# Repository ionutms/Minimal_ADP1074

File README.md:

# Minimal_ADP1074

## Overview

This repository contains a minimal KiCad design project for the Analog Devices ADP1074, a current mode synchronous flyback controller with iCoupler-isolated feedback. The project includes schematic designs and PCB layout files for implementing this isolated power supply controller.

## Disclaimer

> [!NOTE]
> This project is provided "as is" and without any warranty, express or implied. For more details, please see the [LICENSE](LICENSE) file.

## About the ADP1074

The ADP1074 from Analog Devices is a current mode synchronous flyback controller with integrated iCoupler technology for isolated feedback. It is designed for high-efficiency, compact isolated DC-to-DC converters.

Key features include:

- **Integrated iCoupler Technology:** Provides isolated feedback without the need for an optocoupler, improving reliability and performance.
- **Current Mode Control:** Offers excellent line and load transient response.
- **Synchronous Rectification:** Improves efficiency by replacing the secondary-side diode with a MOSFET.
- **Programmable Frequency:** The switching frequency can be adjusted to optimize for size or efficiency.
- **Protection Features:** Includes overcurrent protection (OCP), overvoltage protection (OVP), and thermal shutdown.
- **Wide Input Voltage Range:** Supports a broad range of input voltages, making it suitable for various applications.
- **Package:** Available in a 24-lead LFCSP package.

## Project Structure

```
minimal_adp1074/
├── minimal_adp1074.kicad_pro       # Project configuration file
├── minimal_adp1074.kicad_sch       # Main schematic file
├── minimal_adp1074.kicad_pcb       # PCB layout file
├── fp-lib-table                    # Footprint library table
├── sym-lib-table                   # Symbol library table
├── docs/                           # Documentation files
│   ├── bom/                        # Bill of Materials
│   │   └── minimal_adp1074_ibom.html # Interactive BOM file
│   ├── pictures/                   # Images and photos
│   │   ├── 1_minimal_adp1074_side.png
│   │   ├── 2_minimal_adp1074_top.png
│   │   ├── 3_minimal_adp1074_bottom.png
│   │   ├── 4_minimal_adp1074_left.png
│   │   └── 5_minimal_adp1074_right.png
│   └── schematics/                 # Schematic PDF exports
│       └── minimal_adp1074_schematics.pdf
└── KiCAD_Symbols_Generator/        # Submodule for symbol generation from CSV data
```

## Project Features

This design provides a minimal implementation of the ADP1074 with:

- Proper power supply connections
- Isolated feedback using integrated iCoupler technology
- Synchronous rectification for high efficiency
- Standard footprint for the 24-pin LFCSP package

## Getting Started

### Prerequisites

- [KiCad EDA](https://www.kicad.org/) version 9.0 or later installed on your system
- Git (for cloning the repository and submodule management)

### Opening the Project

1. **Clone the repository** (including submodules):
   ```bash
   git clone --recursive https://github.com/ionutms/Minimal_ADP1074.git
   ```
   
   If you've already cloned the repository without submodules, initialize them with:
   ```bash
   git submodule init
   git submodule update
   ```

2. **Open the project in KiCad**:
   - Launch KiCad
   - Click "Open Existing Project"
   - Navigate to the cloned repository folder
   - Select the `minimal_adp1074.kicad_pro` file

3. **Explore the design**:
   - Open the schematic editor to view the circuit design
   - Open the PCB editor to view the board layout
   - Review the symbol and footprint libraries used in the design

### Project Files

- **Main schematic**: `minimal_adp1074.kicad_sch` - Contains the primary circuit design with the ADP1074 and support components
- **PCB layout**: `minimal_adp1074.kicad_pcb` - Physical board design file with proper component placement
- **Project configuration**: `minimal_adp1074.kicad_pro` - KiCad project settings

## Dependencies

This project has the following dependencies:

### 1. KiCAD Symbols Generator

This repository uses [KiCAD_Symbols_Generator](https://github.com/ionutms/KiCAD_Symbols_Generator) as a submodule for custom symbol generation.

To initialize the submodule after cloning this repository:

```bash
git submodule update --init --recursive
```

### 2. 3D Models

This project requires the [3D_Models_Vault](https://github.com/ionutms/3D_Models_Vault) repository for 3D models.

#### Setup for KiCAD 9:

1. Clone the 3D models repository:
   ```bash
   git clone https://github.com/ionutms/3D_Models_Vault.git
   ```

2. In KiCAD 9, add an environment variable:
   - Variable name: `KICAD9_3D_MODELS_VAULT`
   - Variable value: Full path to where you cloned the 3D_Models_Vault repository

## Usage

After setting up the dependencies, open the project in KiCad 9 to access all features including the 3D models.

## Symbol Generator Submodule

This project includes the KiCAD_Symbols_Generator as a submodule, which provides tools for generating KiCad symbols from CSV data files. For more information on using this tool, see the [KiCAD_Symbols_Generator documentation](minimal_adp1074/KiCAD_Symbols_Generator/README.md).

## Documentation

The `docs` folder contains:
- Schematic PDF exports
- Images and photos of the design

## Visuals

The following images showcase the PCB design from different perspectives:

*Top View of the PCB*

*Side View of the PCB*

*Bottom View of the PCB*

*Left View of the PCB*

*Right View of the PCB*

## License

This project is licensed under the MIT License - see the [LICENSE](LICENSE) file for details.

## References

- [ADP1074 Datasheet](https://www.analog.com/media/en/technical-documentation/data-sheets/ADP1074.pdf)
- [KiCad EDA](https://www.kicad.org/)

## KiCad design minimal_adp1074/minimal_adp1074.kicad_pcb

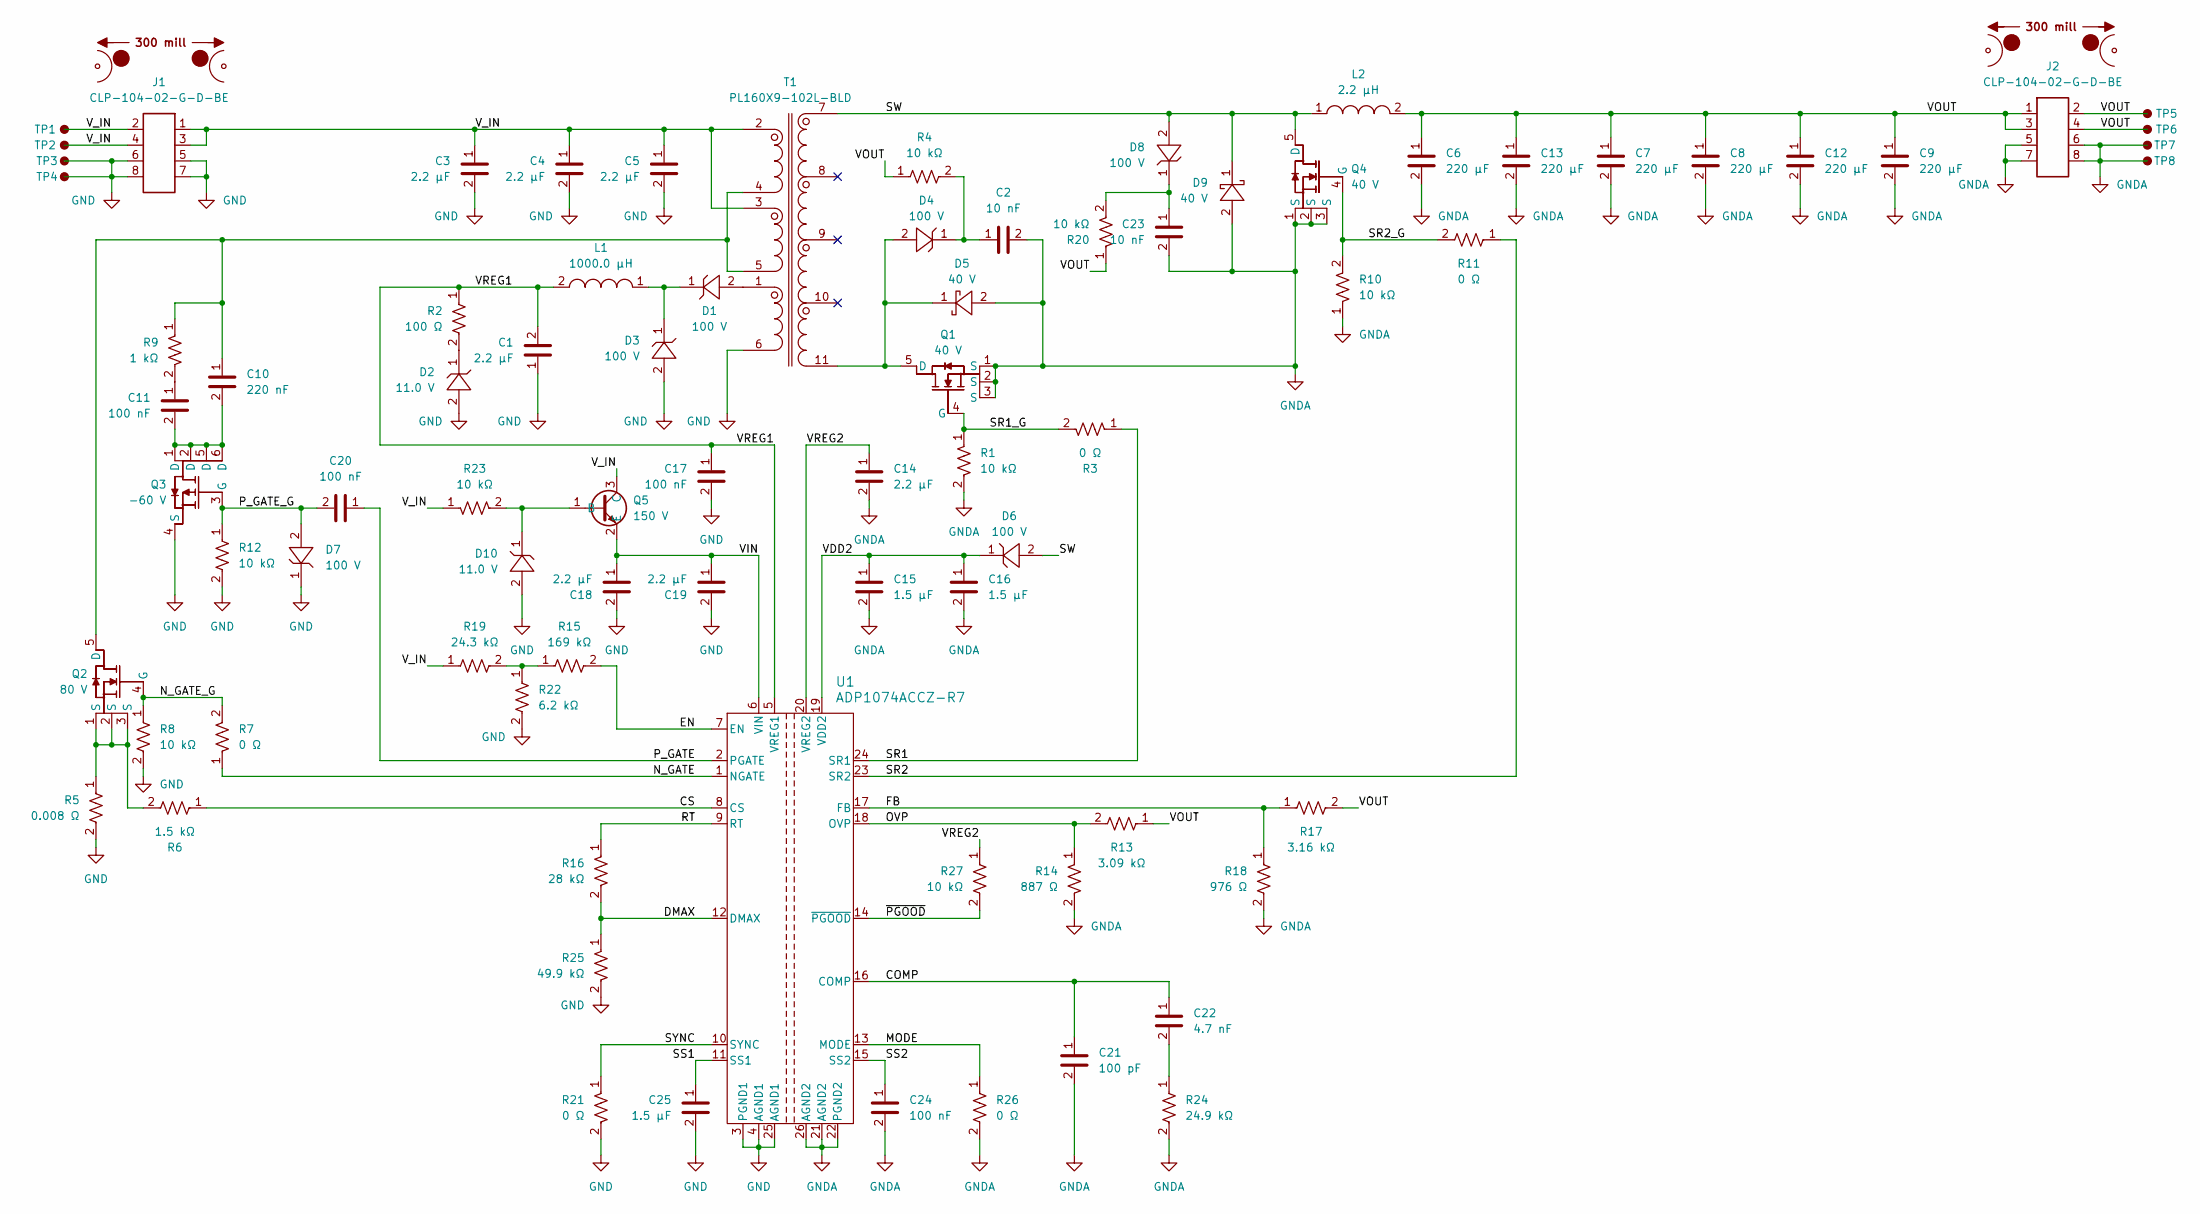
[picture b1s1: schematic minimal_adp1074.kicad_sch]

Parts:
C1, C14, C18, C19: 2.2 µF; C_0603_1608Metric; Tolerance 20%; Voltage Rating 35V; MPN C1005X5R1V225M050BC
C2, C23: 10 nF; C_0402_1005Metric; Tolerance 10%; Voltage Rating 50V; MPN GCM155R71H103KA55D
C3, C4, C5: 2.2 µF; C_1206_3216Metric; Tolerance 10%; Voltage Rating 50V; MPN KGM31HR71H225KU
C6, C7, C8, C9, C12, C13: 220 µF; C_1206_3216Metric; Tolerance 20%; Voltage Rating 6.3V; MPN GRM31CR60J227ME11K
C10: 220 nF; C_0603_1608Metric; Tolerance 10%; Voltage Rating 50V; MPN GCM188R71H224KA64D
C11, C17, C20, C24: 100 nF; C_0402_1005Metric; Tolerance 10%; Voltage Rating 50V; MPN GCM155R71H104KE02D
C15, C16, C25: 1.5 µF; C_0603_1608Metric; Tolerance 20%; Voltage Rating 35V; MPN C1005X5R1V155M050BC
C21: 100 pF; C_0402_1005Metric; Tolerance 1%; Voltage Rating 50V; MPN GCM1555C1H101FA16D
C22: 4.7 nF; C_0402_1005Metric; Tolerance 10%; Voltage Rating 50V; MPN GCM155R71H472KA37D
D1, D3, D4, D6, D7, D8: 100 V; SOD323; MPN 1N4148WX-TP
D2, D10: 11.0 V; SOD_123; MPN BZT52C11-7-F
D5, D9: 40 V; SMA; MPN B240A-13-F
J1, J2: CLP-104-02-G-D-BE; Current Rating (A) 5.2; Voltage Rating (V) 300; MPN CLP-104-02-G-D-BE
L1: 1000.0 µH; CB2518T; Tolerance ±10%; MPN CB2518T102K
L2: 2.2 µH; 74439369; Tolerance ±20%; MPN 74439369022
MB1, MB2: mouse-bite-50mil-300mil
Q1, Q4: 40 V; TDSON-8 FL; MPN BSC014N04LSI
Q2: 80 V; PowerPAK SO-8 Single; MPN SIR680DP-T1-RE3
Q3: -60 V; SOT-26; MPN ZXMP6A17E6TA
Q5: 150 V; SOT23-3; MPN FMMT625TA
R1, R4, R8, R10, R12, R20, R23, R27: 10 kΩ; R_0402_1005Metric; Tolerance 1%; Voltage Rating 50V; MPN ERJ-2RKF1002X
R2: 100 Ω; R_0402_1005Metric; Tolerance 1%; Voltage Rating 50V; MPN ERJ-2RKF1000X
R3, R7, R11, R21, R26: 0 Ω; R_0402_1005Metric; Tolerance 5%; Voltage Rating 50V; MPN ERJ-2GE0R00X
R5: 0.008 Ω; R_1206_3216Metric; Tolerance 1%; Voltage Rating 200V; MPN PMR18EZPFU8L00
R6: 1.5 kΩ; R_0402_1005Metric; Tolerance 1%; Voltage Rating 50V; MPN ERJ-2RKF1501X
R9: 1 kΩ; R_0402_1005Metric; Tolerance 1%; Voltage Rating 50V; MPN ERJ-2RKF1001X
R13: 3.09 kΩ; R_0402_1005Metric; Tolerance 1%; Voltage Rating 50V; MPN ERJ-2RKF3091X
R14: 887 Ω; R_0402_1005Metric; Tolerance 1%; Voltage Rating 50V; MPN ERJ-2RKF8870X
R15: 169 kΩ; R_0402_1005Metric; Tolerance 1%; Voltage Rating 50V; MPN ERJ-2RKF1693X
R16: 28 kΩ; R_0402_1005Metric; Tolerance 1%; Voltage Rating 50V; MPN ERJ-2RKF2802X
R17: 3.16 kΩ; R_0402_1005Metric; Tolerance 1%; Voltage Rating 50V; MPN ERJ-2RKF3161X
R18: 976 Ω; R_0402_1005Metric; Tolerance 1%; Voltage Rating 50V; MPN ERJ-2RKF9760X
R19: 24.3 kΩ; R_0402_1005Metric; Tolerance 1%; Voltage Rating 50V; MPN ERJ-2RKF2432X
R22: 6.2 kΩ; R_0402_1005Metric; Tolerance 1%; Voltage Rating 50V; MPN ERJ-2RKF6201X
R24: 24.9 kΩ; R_0402_1005Metric; Tolerance 1%; Voltage Rating 50V; MPN ERJ-2RKF2492X
R25: 49.9 kΩ; R_0402_1005Metric; Tolerance 1%; Voltage Rating 50V; MPN ERJ-2RKF4992X
T1: PL160X9-102L-BLD; PL160X9-102L; Tolerance ±10%; MPN PL160X9-102L-BLD
TP1, TP2, TP3, TP4, TP5, TP6, TP7, TP8: TestPoint; TestPoint_THTPad_Castelated
U1: ADP1074ACCZ-R7; CC-24-6_ADI; MPN ADP1074ACCZ-R7

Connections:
/COMP: C21.1, C22.1, U1.16 (COMP)
/CS: R6.1, U1.8 (CS)
/DMAX: R16.2, R25.1, U1.12 (DMAX)
/EN: R15.2, U1.7 (EN)
/FB: R17.1, R18.1, U1.17 (FB)
/MODE: R26.1, U1.13 (MODE)
/N_GATE: R7.1, U1.1 (NGATE)
/N_GATE_G: Q2.4 (G), R7.2, R8.1
/OVP: R13.2, R14.1, U1.18 (OVP)
/P_GATE: C20.1, U1.2 (PGATE)
/P_GATE_G: C20.2, D7.2, Q3.3 (G), R12.1
/RT: R16.1, U1.9 (RT)
/SR1: R3.1, U1.24 (SR1)
/SR1_G: Q1.4 (G), R1.1, R3.2
/SR2: R11.1, U1.23 (SR2)
/SR2_G: Q4.4 (G), R10.2, R11.2
/SS1: C25.1, U1.11 (SS1)
/SS2: C24.1, U1.15 (SS2)
/SW: D6.2, D8.2, D9.1, L2.1, Q4.5 (D), T1.7
/SYNC: R21.1, U1.10 (SYNC)
/VDD2: C15.1, C16.1, D6.1, U1.19 (VDD2)
/VIN: C18.1, C19.1, Q5.2 (E), U1.6 (VIN)
/VOUT: C6.1, C7.1, C8.1, C9.1, C12.1, C13.1, J2.1, J2.2, J2.3, J2.4, L2.2, R4.1, R13.1, R17.2, R20.1, TP5.1, TP6.1
/VREG1: C1.2, C17.1, L1.2, R2.1, U1.5 (VREG1)
/VREG2: C14.1, R27.1, U1.20 (VREG2)
/V_IN: C3.1, C4.1, C5.1, J1.1, J1.2, J1.3, J1.4, Q5.3 (C), R19.1, R23.1, T1.2, T1.3, TP1.1, TP2.1
/~PGOOD: R27.2, U1.14 (~PGOOD)
GND: C1.1, C3.2, C4.2, C5.2, C17.2, C18.2, C19.2, C25.2, D2.2, D3.2, D7.1, D10.2, J1.5, J1.6, J1.7, J1.8, Q3.4 (S), R5.2, R8.2, R12.2, R21.2, R22.2, R25.2, T1.6, TP3.1, TP4.1, U1.3 (PGND1), U1.4 (AGND1), U1.25 (AGND1)
GNDA: C2.2, C6.2, C7.2, C8.2, C9.2, C12.2, C13.2, C14.2, C15.2, C16.2, C21.2, C23.2, C24.2, D5.2, D9.2, J2.5, J2.6, J2.7, J2.8, Q1.1 (S), Q1.2 (S), Q1.3 (S), Q4.1 (S), Q4.2 (S), Q4.3 (S), R1.2, R10.1, R14.2, R18.2, R24.2, R26.2, TP7.1, TP8.1, U1.21 (AGND2), U1.22 (PGND2), U1.26 (AGND2)
unnamed: C2.1, D4.1, R4.2
unnamed: C10.2, C11.2, Q3.1 (D), Q3.2 (D), Q3.5 (D), Q3.6 (D)
unnamed: C11.1, R9.2
unnamed: C22.2, R24.1
unnamed: C23.1, D8.1, R20.2
unnamed: D1.1, D3.1, L1.1
unnamed: D1.2, T1.1
unnamed: D2.1, R2.2
unnamed: D4.2, D5.1, Q1.5 (D), T1.11
unnamed: C10.1, Q2.5 (D), R9.1, T1.4, T1.5
unnamed: Q2.1 (S), Q2.2 (S), Q2.3 (S), R5.1, R6.2
unnamed: D10.1, Q5.1 (B), R23.2
unnamed: R15.1, R19.2, R22.1

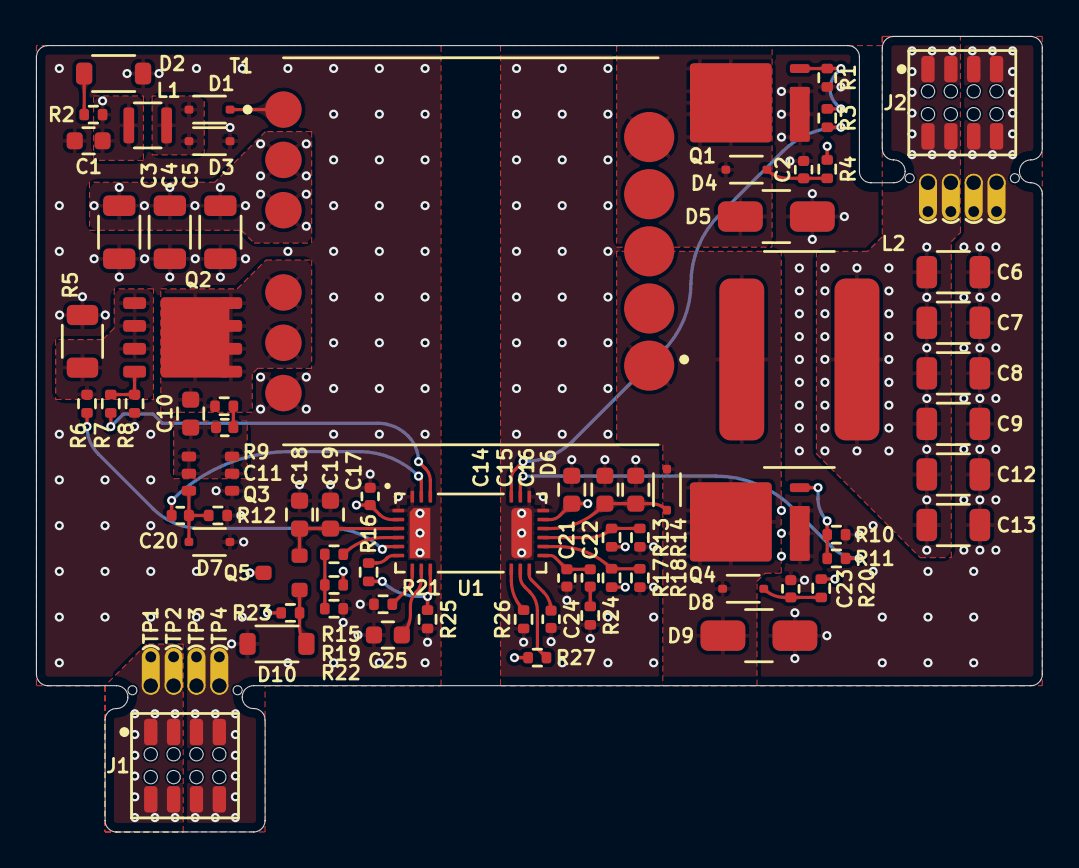
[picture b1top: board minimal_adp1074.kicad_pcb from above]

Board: 4 copper layers, 55.9 x 44.2 mm, 83 parts (0 on the bottom side), 42 nets.

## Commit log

2025-09-21 Add KiCAD project files and submodule for symbol generation
2025-09-21 Add GitHub Actions workflows for KiCad documentation and 3D model generation
2025-09-21 backup
2025-09-21 Update KiCad documentation for minimal_adp1074 (schematics and PCB renders)
2025-09-21 Update KiCAD view settings to 1:1 zoom ratio and center views
2025-09-25 Update README.md with comprehensive documentation
2025-10-04 Add trigger-symbol-check workflow
2025-10-04 Update GitHub workflow files
2025-10-05 Remove push trigger for docs/pictures paths from symbol check workflow
2025-10-05 chore: update workflows from central repository
2025-10-12 chore: update workflows and kicad config from central repository
